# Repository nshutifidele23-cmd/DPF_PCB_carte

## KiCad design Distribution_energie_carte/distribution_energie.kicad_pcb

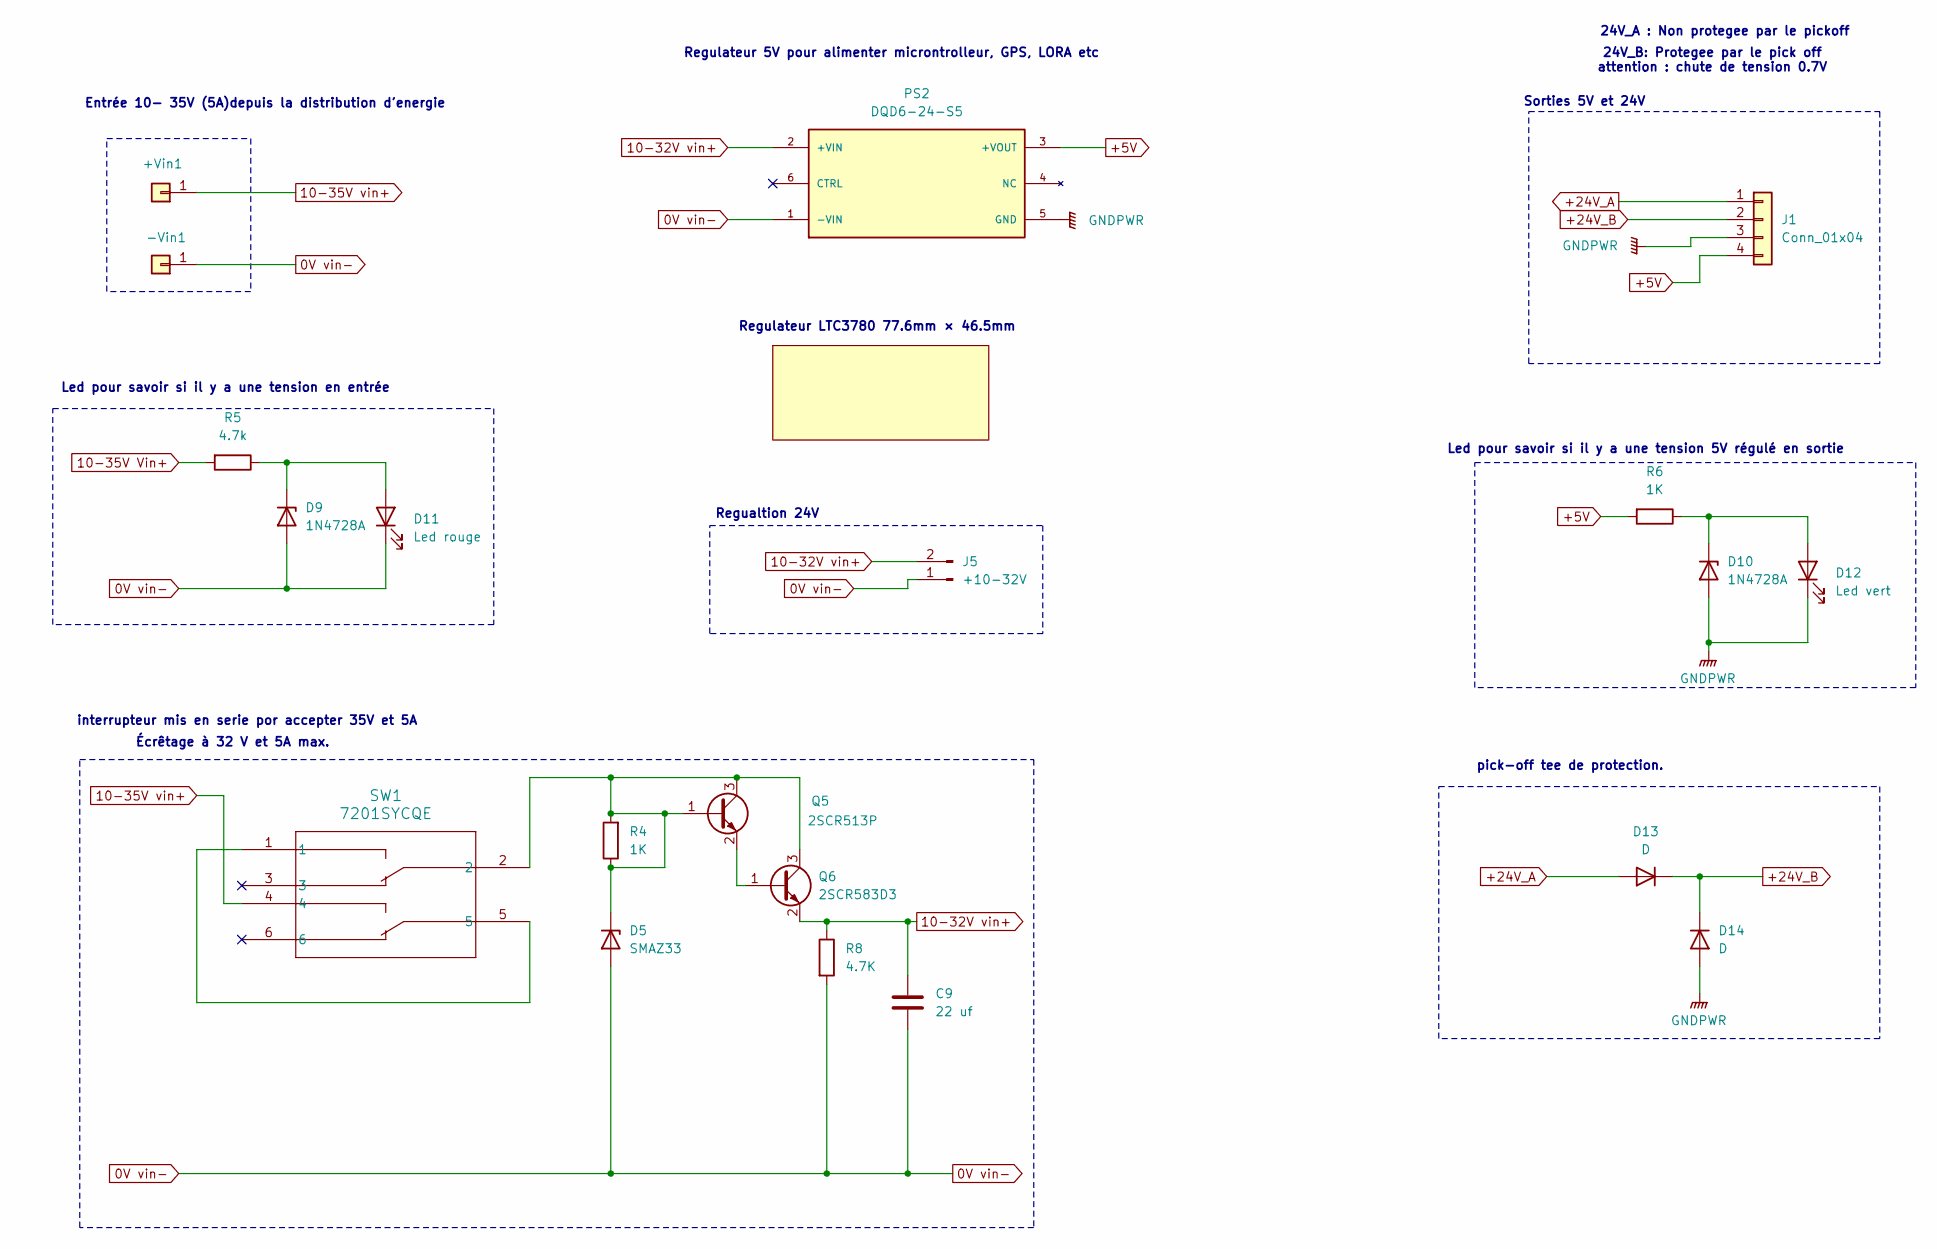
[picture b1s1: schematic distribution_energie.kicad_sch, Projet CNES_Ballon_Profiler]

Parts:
+Vin1: +vin_10v_35V; SolderWire-1sqmm_1x01_D1.4mm_OD2.7mm
-Vin1: -Vin_10v_35V; SolderWire-1sqmm_1x01_D1.4mm_OD2.7mm
C9: 22 uf; C_0805_2012Metric
D5: SMAZ33; D_SMA_Handsoldering
D9, D10: 1N4728A; D_DO-41_SOD81_P10.16mm_Horizontal
D11: Led rouge; LED_1206_3216Metric_Pad1.42x1.75mm_HandSolder
D12: Led vert; LED_1206_3216Metric_Pad1.42x1.75mm_HandSolder
D13, D14: D; D_SMC_Handsoldering
J1: Conn_01x04; PinHeader_1x04_P2.54mm_Vertical
J5: +10-32V; TerminalBlock_Phoenix_MKDS-1,5-2-5.08_1x02_P5.08mm_Horizont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
PS2: DQD6-24-S5; CONV_DQD6-24-S5; MPN DQD6-24-S5
Q5: 2SCR513P; SOT-89-3
Q6: 2SCR583D3; TO-252-3_TabPin2
R4, R6: 1K; R_0805_2012Metric_Pad1.20x1.40mm_HandSolder
R5: 4.7k; R_0805_2012Metric_Pad1.20x1.40mm_HandSolder
R8: 4.7K; R_0805_2012Metric_Pad1.20x1.40mm_HandSolder
Regulateur_Ltc3780: Regulateur LTC3780
SW1: 7201SYCQE; sw1

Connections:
0V vin-: -Vin1.1 (Pin_1_1), C9.2, D5.2 (A), D9.2 (A), D11.1 (K), J5.1, PS2.1 (-VIN), R8.2
10-32V vin+: C9.1, J5.2, PS2.2 (+VIN), Q6.2 (E), R8.1
10-35V Vin+: R5.2
10-35V vin+: +Vin1.1 (Pin_1_1), SW1.4
+5V: J1.4, PS2.3 (+VOUT), R6.2
+24V_A: D13.2 (A), J1.1
+24V_B: D13.1 (K), D14.1 (K), J1.2
GNDPWR: D10.2 (A), D12.1 (K), D14.2 (A), J1.3, PS2.5 (GND)
unnamed: D5.1 (K), Q5.1 (B), Q5.3 (C), Q6.3 (C), R4.1, R4.2, SW1.2
unnamed: D10.1 (K), D12.2 (A), R6.1
unnamed: D9.1 (K), D11.2 (A), R5.1
unnamed: Q5.2 (E), Q6.1 (B)
unnamed: SW1.1, SW1.5

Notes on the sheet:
Écrêtage à 32 V et 5A max.
Regulateur 5V pour alimenter microntrolleur, GPS, LORA etc
24V_A : Non protegee par le pickoff
24V_B: Protegee par le pick off attention : chute de tension 0.7V
interrupteur mis en serie por accepter 35V et 5A
pick-off tee de protection.
Led pour savoir si il y a une tension en entrée
Regulateur LTC3780 77.6mm × 46.5mm
Entrée 10- 35V (5A)depuis la distribution d'energie
Sorties 5V et 24V
Led pour savoir si il y a une tension 5V régulé en sortie
Regualtion 24V

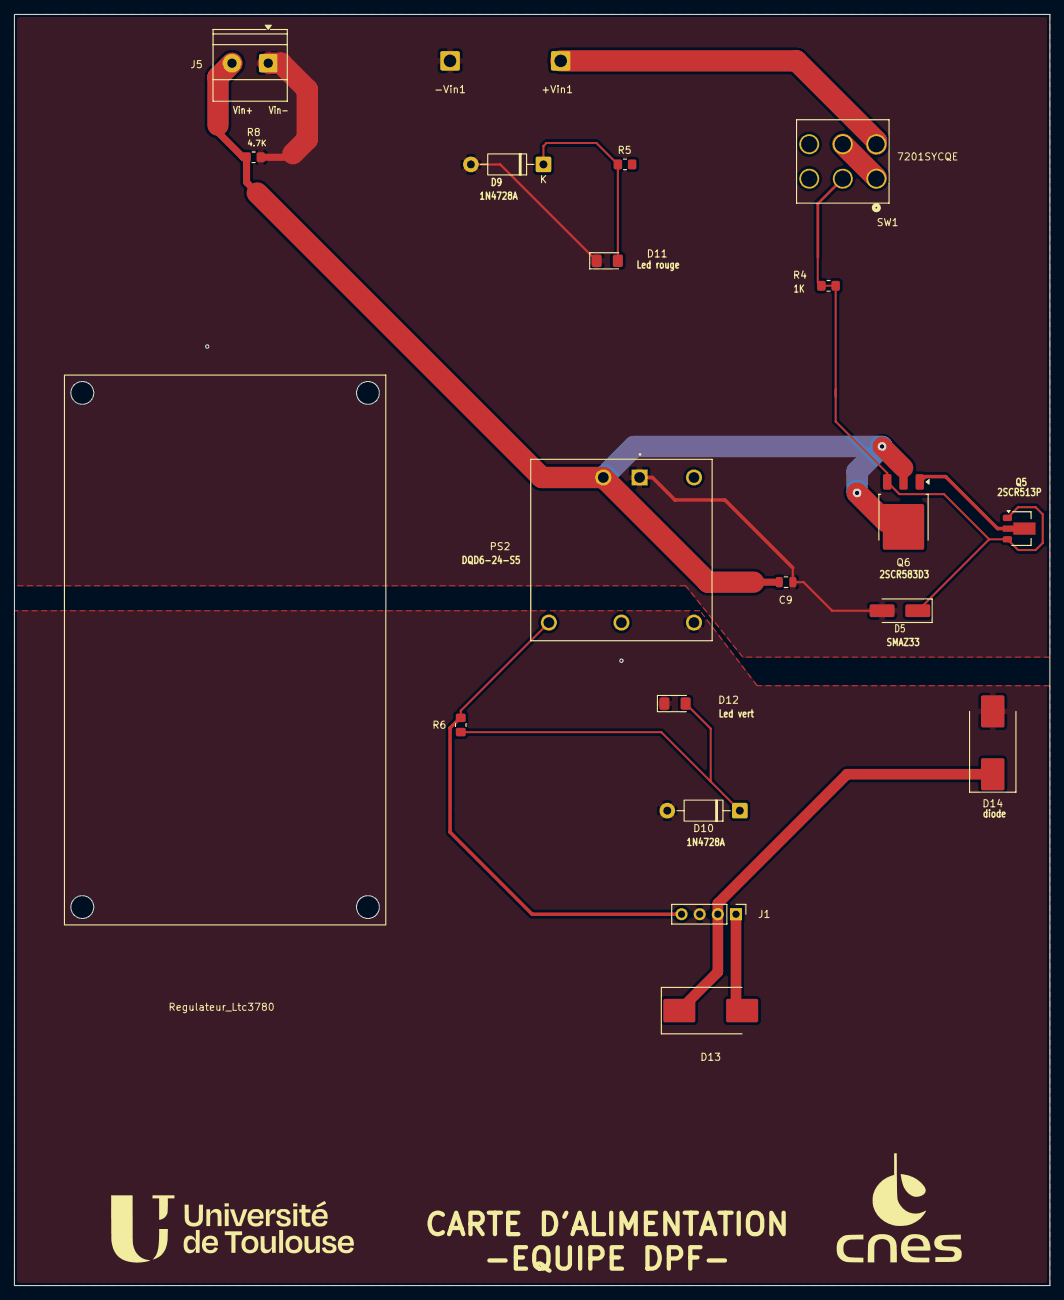
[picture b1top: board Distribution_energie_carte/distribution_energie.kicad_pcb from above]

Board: 2 copper layers, 145.0 x 178.0 mm, 21 parts (0 on the bottom side), 12 nets.

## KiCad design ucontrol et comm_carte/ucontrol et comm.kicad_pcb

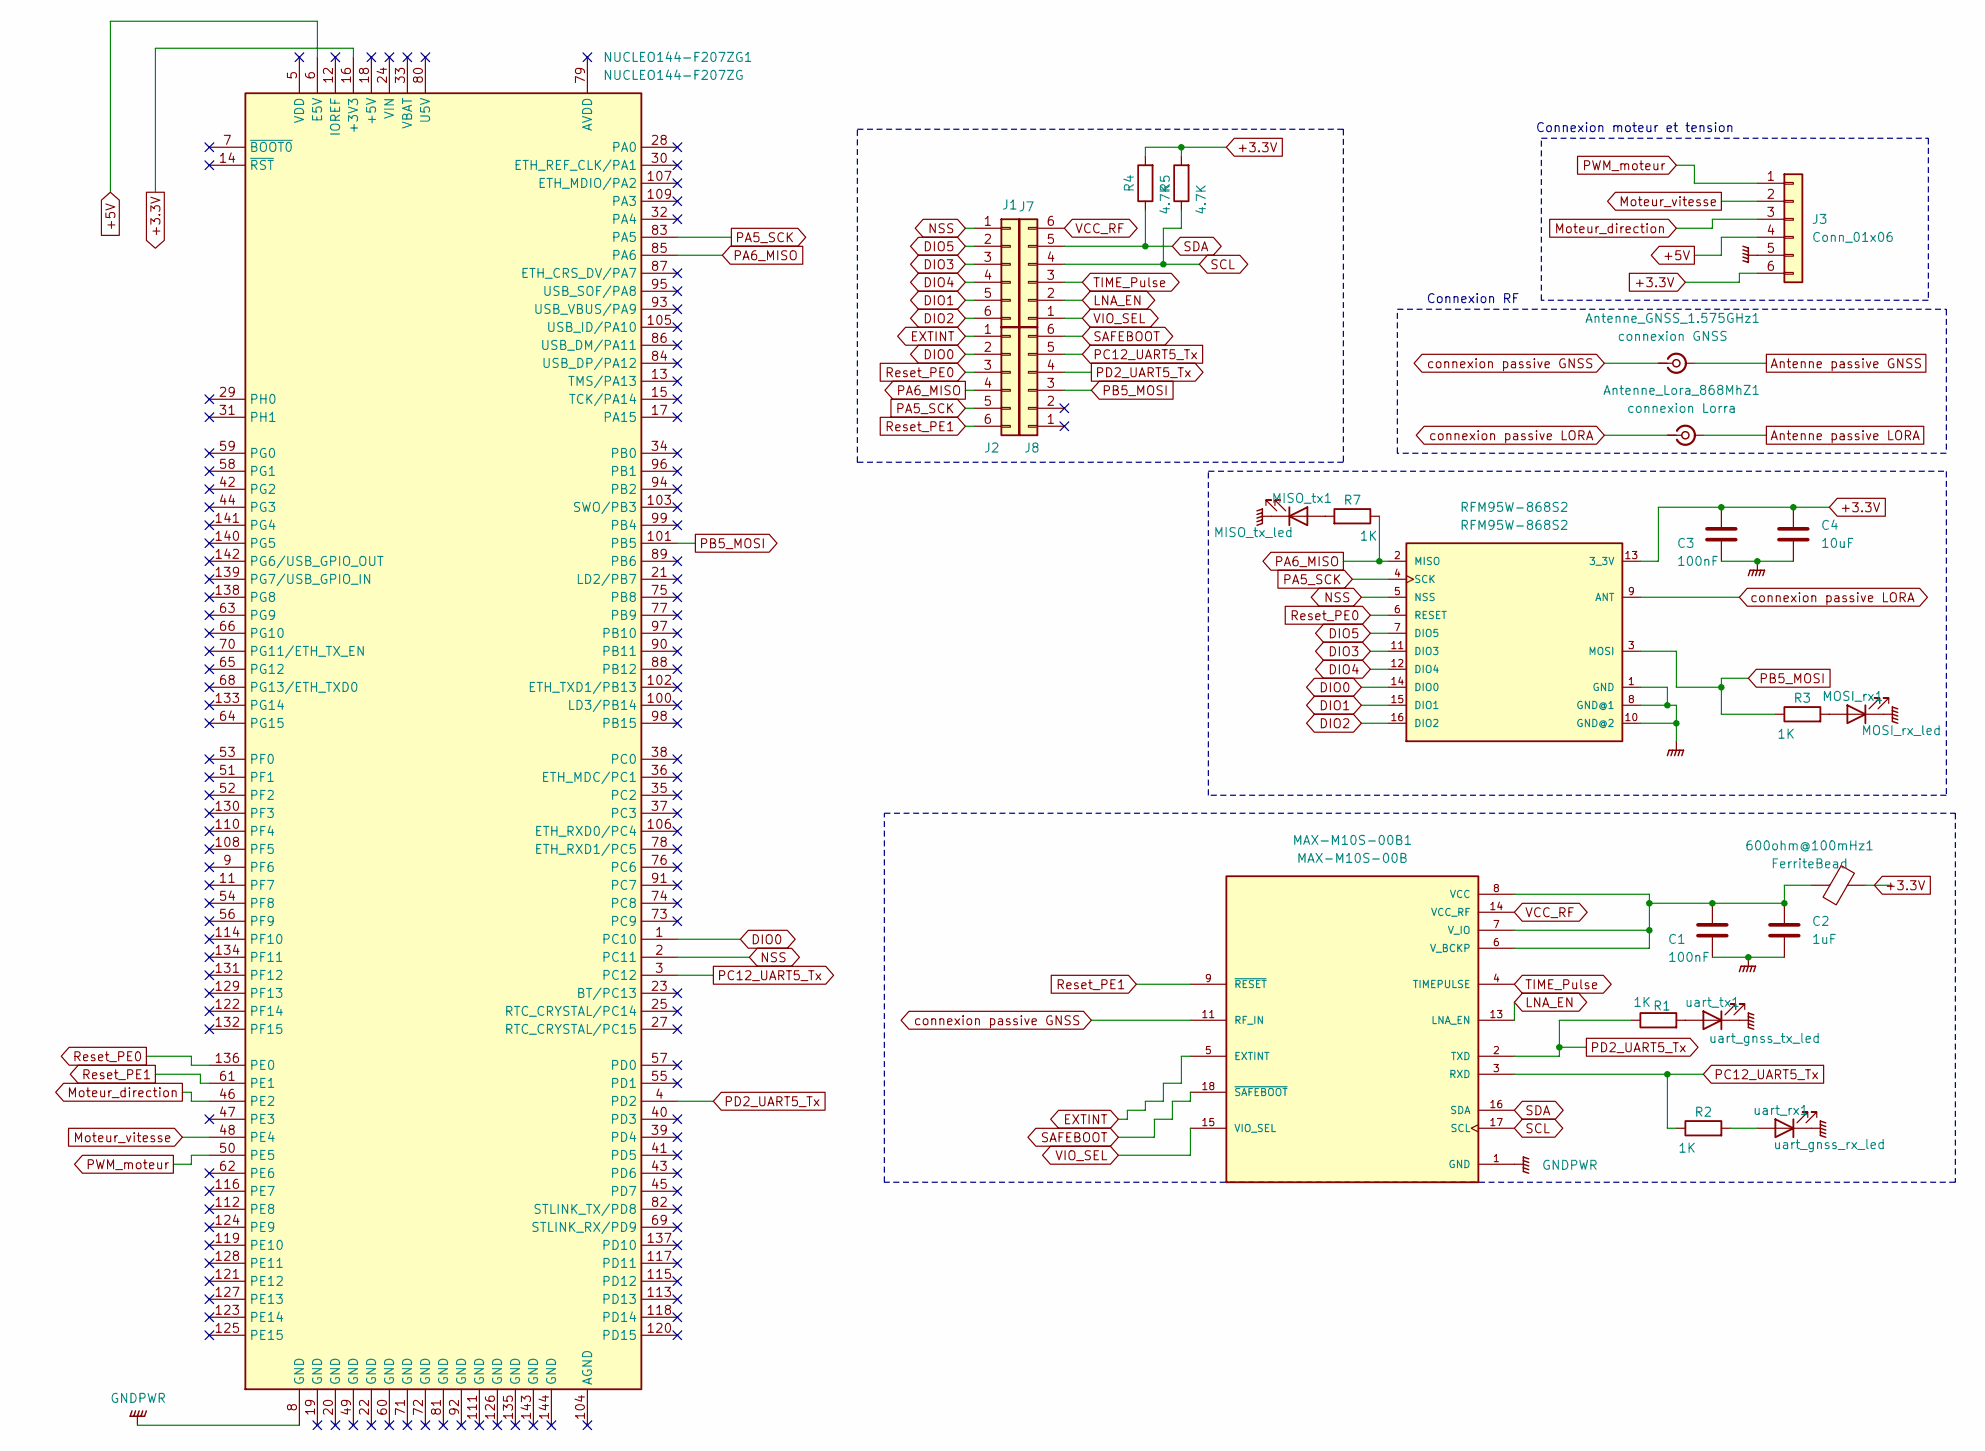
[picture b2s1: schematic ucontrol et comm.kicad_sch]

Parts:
600ohm@100mHz1: FerriteBead; L_0805_2012Metric_Pad1.05x1.20mm_HandSolder
Antenne_GNSS_1.575GHz1: connexion GNSS; SMA_Molex_73251-1153_EdgeMount_Horizontal
Antenne_Lora_868MhZ1: connexion Lorra; SMA_Molex_73251-1153_EdgeMount_Horizontal
C1, C3: 100nF; C_0603_1608Metric_Pad1.08x0.95mm_HandSolder
C2: 1uF; C_0603_1608Metric_Pad1.08x0.95mm_HandSolder
C4: 10uF; C_0603_1608Metric_Pad1.08x0.95mm_HandSolder
J1, J2, J7, J8: Conn_01x06; PinHeader_1x06_P2.54mm_Vertical
J3: Conn_01x06; PinHeader_1x06_P2.54mm_Horizontal
MAX-M10S-00B1: MAX-M10S-00B; XCVR_MAX-M10S-00B; MPN MAX-M10S-00B
MISO_tx1: MISO_tx_led; LED_1206_3216Metric_Pad1.42x1.75mm_HandSolder
MOSI_rx1: MOSI_rx_led; LED_1206_3216Metric_Pad1.42x1.75mm_HandSolder
NUCLEO144-F207ZG1: NUCLEO144-F207ZG; ST_Morpho_Connector_144_STLink
R1, R2, R3, R7: 1K; R_0805_2012Metric_Pad1.20x1.40mm_HandSolder
R4, R5: 4.7K; R_0805_2012Metric_Pad1.20x1.40mm_HandSolder
RFM95W-868S2: RFM95W-868S2; XCVR_RFM95W-868S2; MPN RFM95W-868S2
uart_rx1: uart_gnss_rx_led; LED_1206_3216Metric_Pad1.42x1.75mm_HandSolder
uart_tx1: uart_gnss_tx_led; LED_1206_3216Metric_Pad1.42x1.75mm_HandSolder

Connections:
Antenne passive LORA: Antenne_Lora_868MhZ1.2 (Ext)
+3.3V: 600ohm@100mHz1.1, C3.1, C4.1, J3.6, NUCLEO144-F207ZG1.16 (+3V3), R4.2, R5.2, RFM95W-868S2.13 (3_3V)
+5V: J3.4, NUCLEO144-F207ZG1.6 (E5V)
Antenne passive GNSS: Antenne_GNSS_1.575GHz1.2 (Ext)
DIO0: J2.2, NUCLEO144-F207ZG1.1 (PC10), RFM95W-868S2.14 (DIO0)
DIO1: J1.5, RFM95W-868S2.15 (DIO1)
DIO2: J1.6, RFM95W-868S2.16 (DIO2)
DIO3: J1.3, RFM95W-868S2.11 (DIO3)
DIO4: J1.4, RFM95W-868S2.12 (DIO4)
DIO5: J1.2, RFM95W-868S2.7 (DIO5)
EXTINT: J2.1, MAX-M10S-00B1.5 (EXTINT)
GNDPWR: C1.2, C2.2, C3.2, C4.2, J3.5, MAX-M10S-00B1.1 (GND), MAX-M10S-00B1.10 (GND), MAX-M10S-00B1.12 (GND), MISO_tx1.1 (K), MOSI_rx1.1 (K), NUCLEO144-F207ZG1.8 (GND), RFM95W-868S2.1 (GND), RFM95W-868S2.8 (GND@1), RFM95W-868S2.10 (GND@2), uart_rx1.1 (K), uart_tx1.1 (K)
LNA_EN: J7.2, MAX-M10S-00B1.13 (LNA_EN)
Moteur_direction: J3.3, NUCLEO144-F207ZG1.46 (PE2)
Moteur_vitesse: J3.2, NUCLEO144-F207ZG1.48 (PE4)
NSS: J1.1, NUCLEO144-F207ZG1.2 (PC11), RFM95W-868S2.5 (NSS)
unnamed: 600ohm@100mHz1.2, C1.1, C2.1, MAX-M10S-00B1.6 (V_BCKP), MAX-M10S-00B1.7 (V_IO), MAX-M10S-00B1.8 (VCC)
unnamed: MISO_tx1.2 (A), R7.2
unnamed: MOSI_rx1.2 (A), R3.2
unnamed: R2.2, uart_rx1.2 (A)
unnamed: R1.2, uart_tx1.2 (A)
PA5_SCK: J2.5, NUCLEO144-F207ZG1.83 (PA5), RFM95W-868S2.4 (SCK)
PA6_MISO: J2.4, NUCLEO144-F207ZG1.85 (PA6), R7.1, RFM95W-868S2.2 (MISO)
PB5_MOSI: J8.3, NUCLEO144-F207ZG1.101 (PB5), R3.1, RFM95W-868S2.3 (MOSI)
PC12_UART5_Tx: J8.5, MAX-M10S-00B1.3 (RXD), NUCLEO144-F207ZG1.3 (PC12), R2.1
PD2_UART5_Tx: J8.4, MAX-M10S-00B1.2 (TXD), NUCLEO144-F207ZG1.4 (PD2), R1.1
PWM_moteur: J3.1, NUCLEO144-F207ZG1.50 (PE5)
Reset_PE0: J2.3, NUCLEO144-F207ZG1.136 (PE0), RFM95W-868S2.6 (RESET)
Reset_PE1: J2.6, MAX-M10S-00B1.9 (~RESET), NUCLEO144-F207ZG1.61 (PE1)
SAFEBOOT: J8.6, MAX-M10S-00B1.18 (~SAFEBOOT)
SCL: J7.4, MAX-M10S-00B1.17 (SCL), R5.1
SDA: J7.5, MAX-M10S-00B1.16 (SDA), R4.1
TIME_Pulse: J7.3, MAX-M10S-00B1.4 (TIMEPULSE)
VCC_RF: J7.6, MAX-M10S-00B1.14 (VCC_RF)
VIO_SEL: J7.1, MAX-M10S-00B1.15 (VIO_SEL)
connexion passive GNSS: Antenne_GNSS_1.575GHz1.1 (In), MAX-M10S-00B1.11 (RF_IN)
connexion passive LORA: Antenne_Lora_868MhZ1.1 (In), RFM95W-868S2.9 (ANT)

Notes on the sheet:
Connexion moteur et tension
Connexion RF

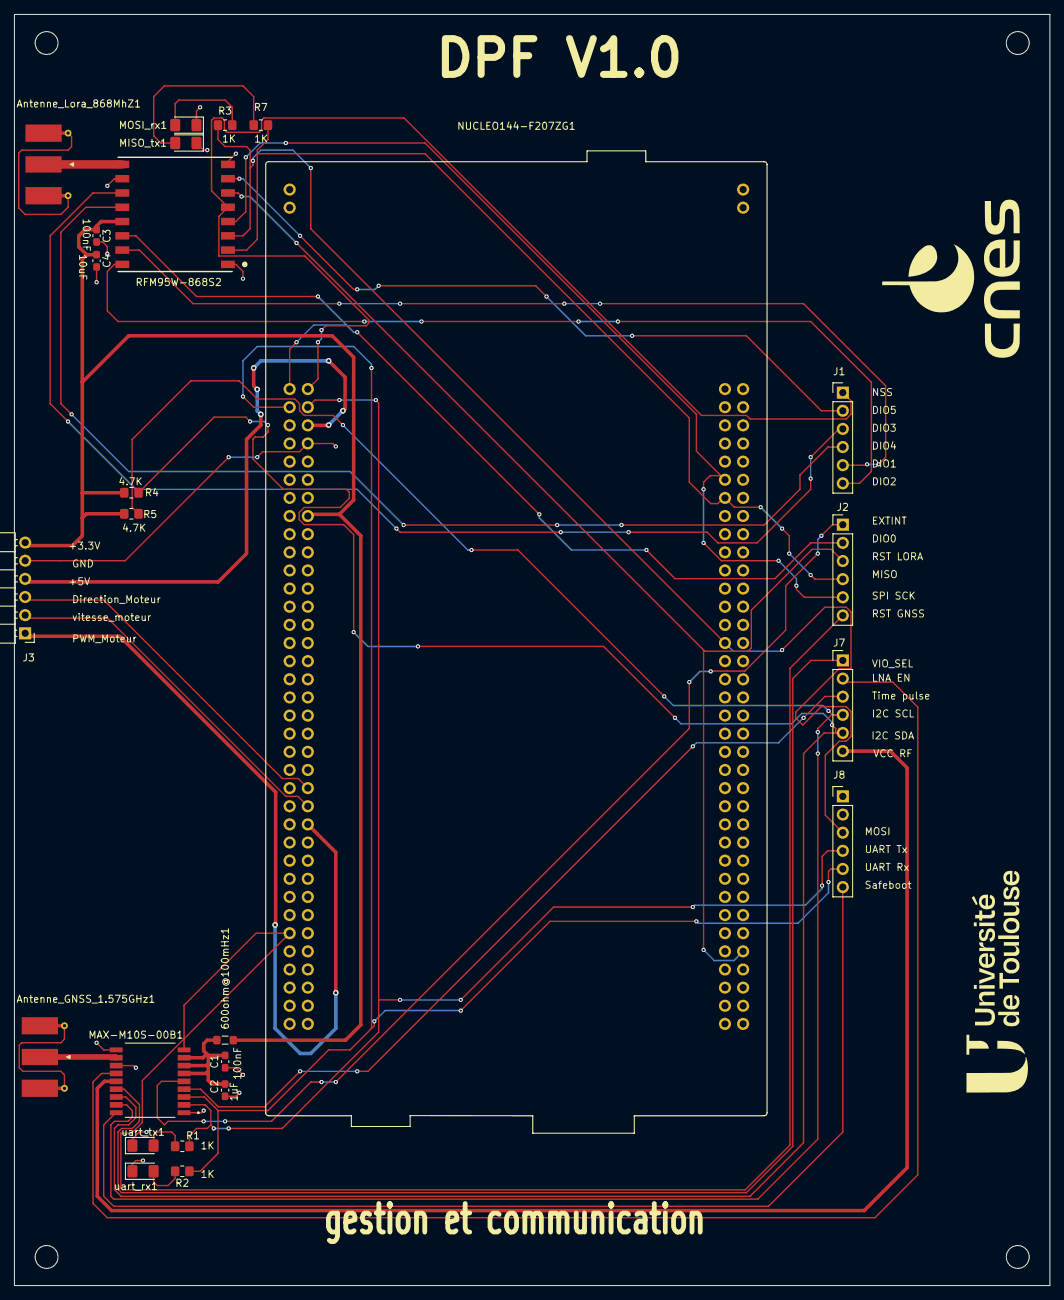
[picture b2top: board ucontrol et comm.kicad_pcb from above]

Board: 2 copper layers, 145.0 x 178.0 mm, 26 parts (0 on the bottom side), 35 nets.

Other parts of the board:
cnes: LOGO

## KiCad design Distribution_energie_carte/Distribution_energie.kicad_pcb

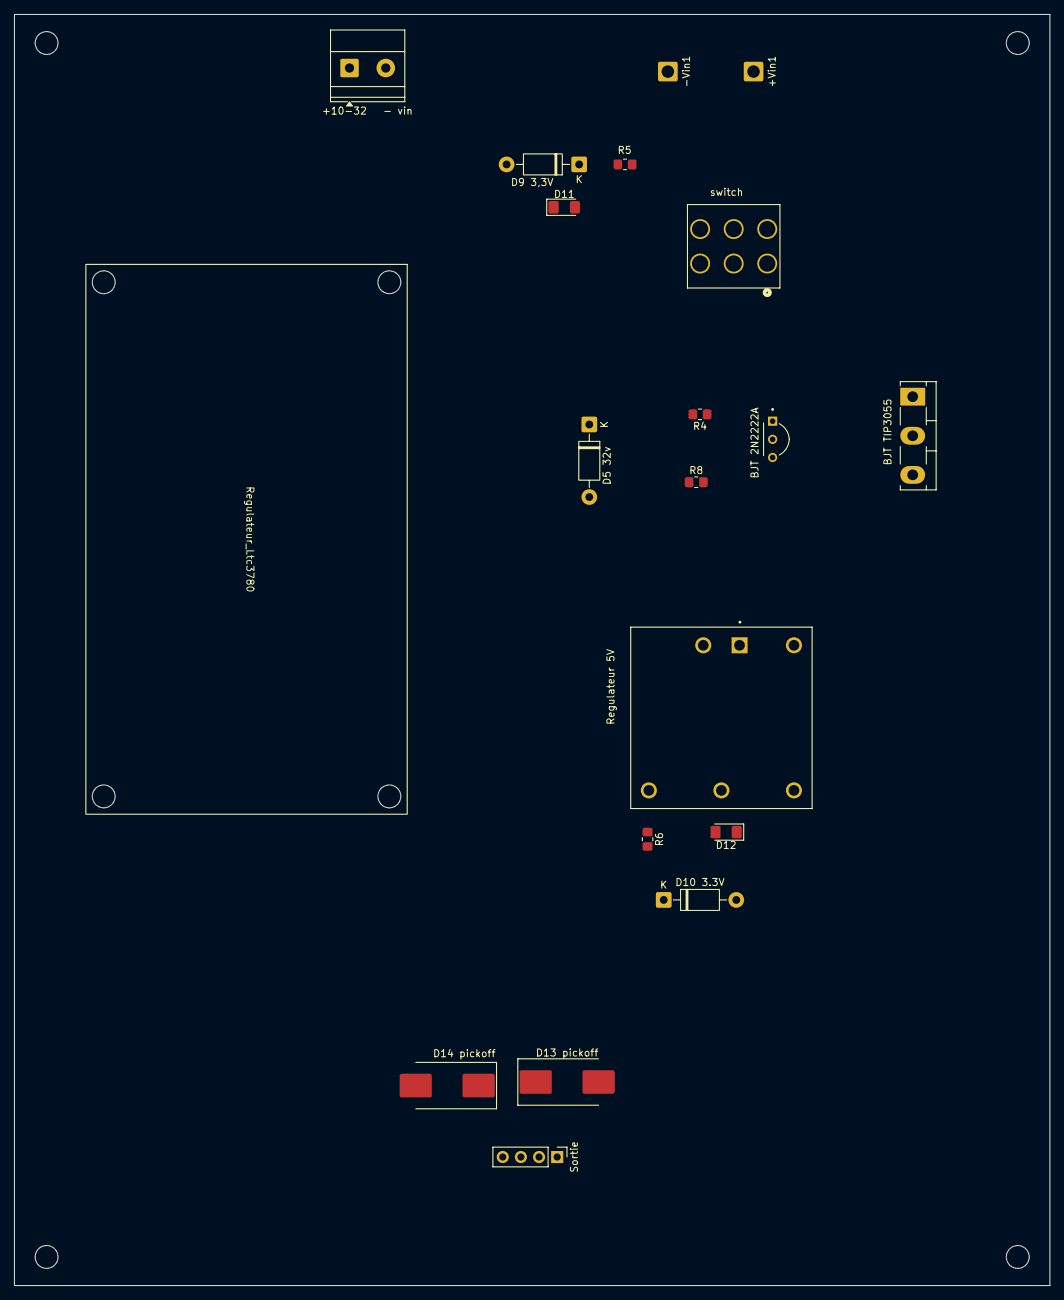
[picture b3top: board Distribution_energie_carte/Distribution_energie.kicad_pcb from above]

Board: 2 copper layers, 145.0 x 178.0 mm, 20 parts (0 on the bottom side), 13 nets, no tracks yet.

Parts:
+10-32   - vin   : +10-32V; TerminalBlock_Phoenix_MKDS-1,5-2-5.08_1x02_P5.08mm_Horizont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
+Vin1: +vin_10v_35V; SolderWire-1sqmm_1x01_D1.4mm_OD2.7mm
-Vin1: -Vin_10v_35V; SolderWire-1sqmm_1x01_D1.4mm_OD2.7mm
BJT 2N2222A: 2N2222A; TO92254P470H750-3
BJT TIP3055: TIP3055; TO-218-3_Vertical
D5 32v: 1N4752A; D_DO-41_SOD81_P10.16mm_Horizontal
D9 3,3V, D10 3.3V: 1N4728A; D_DO-41_SOD81_P10.16mm_Horizontal
D11: Led rouge; LED_1206_3216Metric_Pad1.42x1.75mm_HandSolder
D12: Led vert; LED_1206_3216Metric_Pad1.42x1.75mm_HandSolder
D13 pickoff, D14 pickoff: D; D_SMC_Handsoldering
R4, R6: 1K; R_0805_2012Metric_Pad1.20x1.40mm_HandSolder
R5: 4.7k; R_0805_2012Metric_Pad1.20x1.40mm_HandSolder
R8: 4.7K; R_0805_2012Metric_Pad1.20x1.40mm_HandSolder
Regulateur 5V: DQD6-24-S5; CONV_DQD6-24-S5
Regulateur_Ltc3780: Regulateur LTC3780
Sortie: Conn_01x04; PinHeader_1x04_P2.54mm_Vertical
switch: 7201SYCQE; SW6_7201SYCQE_CNK

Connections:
0V vin-: +10-32 - vin.1, -Vin1.1 (Pin_1_1), D5 32v.2 (A), D9 3,3V.2 (A), D11.1 (K), R8.2, Regulateur 5V.1 (-VIN)
10-32V vin+: +10-32 - vin.2, BJT TIP3055.3 (E), R8.1, Regulateur 5V.2 (+VIN)
10-35V vin+: +Vin1.1 (Pin_1_1), switch.4
+5V: R6.2, Regulateur 5V.3 (+VOUT), Sortie.4
+24V_A: D13 pickoff.2 (A), Sortie.1
+24V_B: D13 pickoff.1 (K), D14 pickoff.1 (K), Sortie.2
GNDPWR: D10 3.3V.2 (A), D12.1 (K), D14 pickoff.2 (A), Regulateur 5V.5 (GND), Sortie.3
unnamed: BJT 2N2222A.2, D5 32v.1 (K), R4.1
unnamed: D10 3.3V.1 (K), D12.2 (A), R6.1
unnamed: D9 3,3V.1 (K), D11.2 (A), R5.1
unnamed: BJT 2N2222A.1, BJT TIP3055.1 (B)
unnamed: BJT 2N2222A.3, BJT TIP3055.2 (C), R4.2, switch.2
unnamed: switch.1, switch.5
